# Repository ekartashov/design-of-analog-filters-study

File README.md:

# Design of Analog Filters

**The analog front-end of a surface-EMG (muscle) sensor — designed, simulated, built and measured.**
Maturità thesis (independent research paper of the Swiss Gymnasium), *Liceo cantonale di Lugano 1*, school year **2021/2022**.

## 📄 Read the paper

| Edition | PDF | |
|---|---|---|
| 🇬🇧 **English** | [`…_EN_optimized.pdf`](LAM/LAM_Design_dei_filtri_analogici/LAM_Design_dei_filtri_analogici_EN_optimized.pdf) | **recommended entry point** |
| 🇮🇹 **Italiano** | [`…_2022-optimized.pdf`](LAM/LAM_Design_dei_filtri_analogici/LAM_Design_dei_filtri_analogici_2022-optimized.pdf) | **the original** |
| 🇷🇺 **Русский** | [`…_RU_optimized.pdf`](LAM/LAM_Design_dei_filtri_analogici/LAM_Design_dei_filtri_analogici_RU_optimized.pdf) | translation |

> **On languages.** The paper was written and submitted in **Italian**; that is the original. The English and Russian editions are complete 2026 re-translations of the same text and figures (AI-assisted, human-revised; interpretation spots are flagged in the sources as `% TRANSLATOR NOTE:` comments). Cite the Italian original.

> **On the context.** This was completed as a **maturità paper for the Gymnasium** (high-school leaving qualification) during the 2021/2022 school year at the Cantonal Lyceum of Lugano (Liceo cantonale di Lugano 1, Switzerland). It was an entirely self-directed project: **no university studies and no related formal courses had informed it** — the filter theory, the circuit design and the measurement methodology were studied independently for this work.

## What this project is

A from-scratch development of the analog signal chain of an electromyographic sensor — the weak muscle signal picked up by skin electrodes, conditioned and digitized:

- **Theory built up from first principles** in the paper: systems, transfer functions, poles/zeros, Bode plots, passive and active filter stages (Butterworth, Chebyshev, Bessel), op-amp circuits, noise/EMI, discretization, ADC resolution
- **Full hardware**: 3 custom PCBs (sensor board, electrode board, power-source board) designed in KiCad, built as photographed prototypes
- **Real measurements**: 8-channel recordings of hand-muscle contractions, with amplitude/height adjustability demonstrated and FFT gesture analysis — including a 66 MB raw acquisition dataset
- **81 pages, 121 natively-drawn plots** (pgfplots — Bode/transient/pole-zero figures compiled from the same CSVs as the measurements), 74 sources

## Repository layout

```
LAM/LAM_Design_dei_filtri_analogici/    the paper: .tex sources, .bib, media/, datasets/, and the 3 optimized PDFs
LAM/secondary/                          working material: filter-design notes, sensor-board diagram, FFT notebooks
kicad/emg_sensor_board/                 hardware project: 3 PCBs + schematics, 3D renders, sim notes, BOM
scripts/devbox/  distrobox.ini          reproducible TeX toolchain (podman + distrobox, image pinned by digest)
notes/                                  provenance and translation-workflow notes
```

## Building the paper

The toolchain is containerized (LuaLaTeX + biber + TeX Live 2025 in a Debian devbox):

```bash
./scripts/devbox/setup-devbox.bash            # build image + create the box (once; requires podman)
distrobox enter devbox_lam_latex -- bash -c '
  cd LAM/LAM_Design_dei_filtri_analogici && latexmk -lualatex -shell-escape'
```

Figures are TikZ-externalized into `cache/` (gitignored) — a cold build renders all ~120 of them once, incremental rebuilds then take minutes. The PDFs committed here are Ghostscript-optimized (~19 MB each, visually lossless); unoptimized builds are ~150 MB and are left out of the repo.

**Cleaning up afterwards.** `scripts/clean.sh` removes the junk a build leaves behind (LaTeX intermediates, `latexmk` strays, the ~150 MB unoptimized PDFs) while keeping the three `_optimized.pdf` deliverables, the 2022 original and all sources; `scripts/clean.sh --deep` additionally drops the `cache/` figures.

**Rebuilding the smaller documents.** The standalone working notes under `LAM/secondary/` (each folder is a tiny LaTeX document: the 8-channel plot sheet `plots/Standalone.tex`, `Q_Factor/`, `Analogue_filter_design/`, `Circuit/SensorBoard_circuit_diagram.tex`) and the KiCad print plot are *build outputs* and are not committed — regenerate them with `latexmk -lualatex -shell-escape <name>.tex` in the devbox, or re-export the plot from the KiCad project. The PDFs that **are** committed under `media/` (Maple exports, Ideasheets, PCB crops, TI app-notes) are *inputs*: the Maple worksheets did not survive, so those ten Maple PDFs are irreplaceable. The `guide/Order_*.pdf` is a JLC order record, kept as a document.

## Measurement datasets

In `LAM/LAM_Design_dei_filtri_analogici/datasets/`:

| Folder | Contents |
|---|---|
| `cf_fft_hand_muscles/` | 8-channel hand-contraction acquisitions (incl. per-session raw dumps and a 66 MB `data.txt`), FFT analysis notebook |
| `result/` | the three plotted measured signals (`gr1`–`gr3.csv` — the teal traces in Fig. 54) |
| `s_plot_example_data/`, `s_plot_log_example_data/` | filter-response datasets behind the Bode/transient plots |
| `ecg_example_data/` | ECG example recorded through the EMG sensor |

## License

© 2021–2026 Evgeny Kartashov — [CC BY 4.0](LICENSE.md). Third-party images (e.g. Arduino/ESP32 board photos, datasheet figures) keep their sources' licenses as credited in the paper's source lists.

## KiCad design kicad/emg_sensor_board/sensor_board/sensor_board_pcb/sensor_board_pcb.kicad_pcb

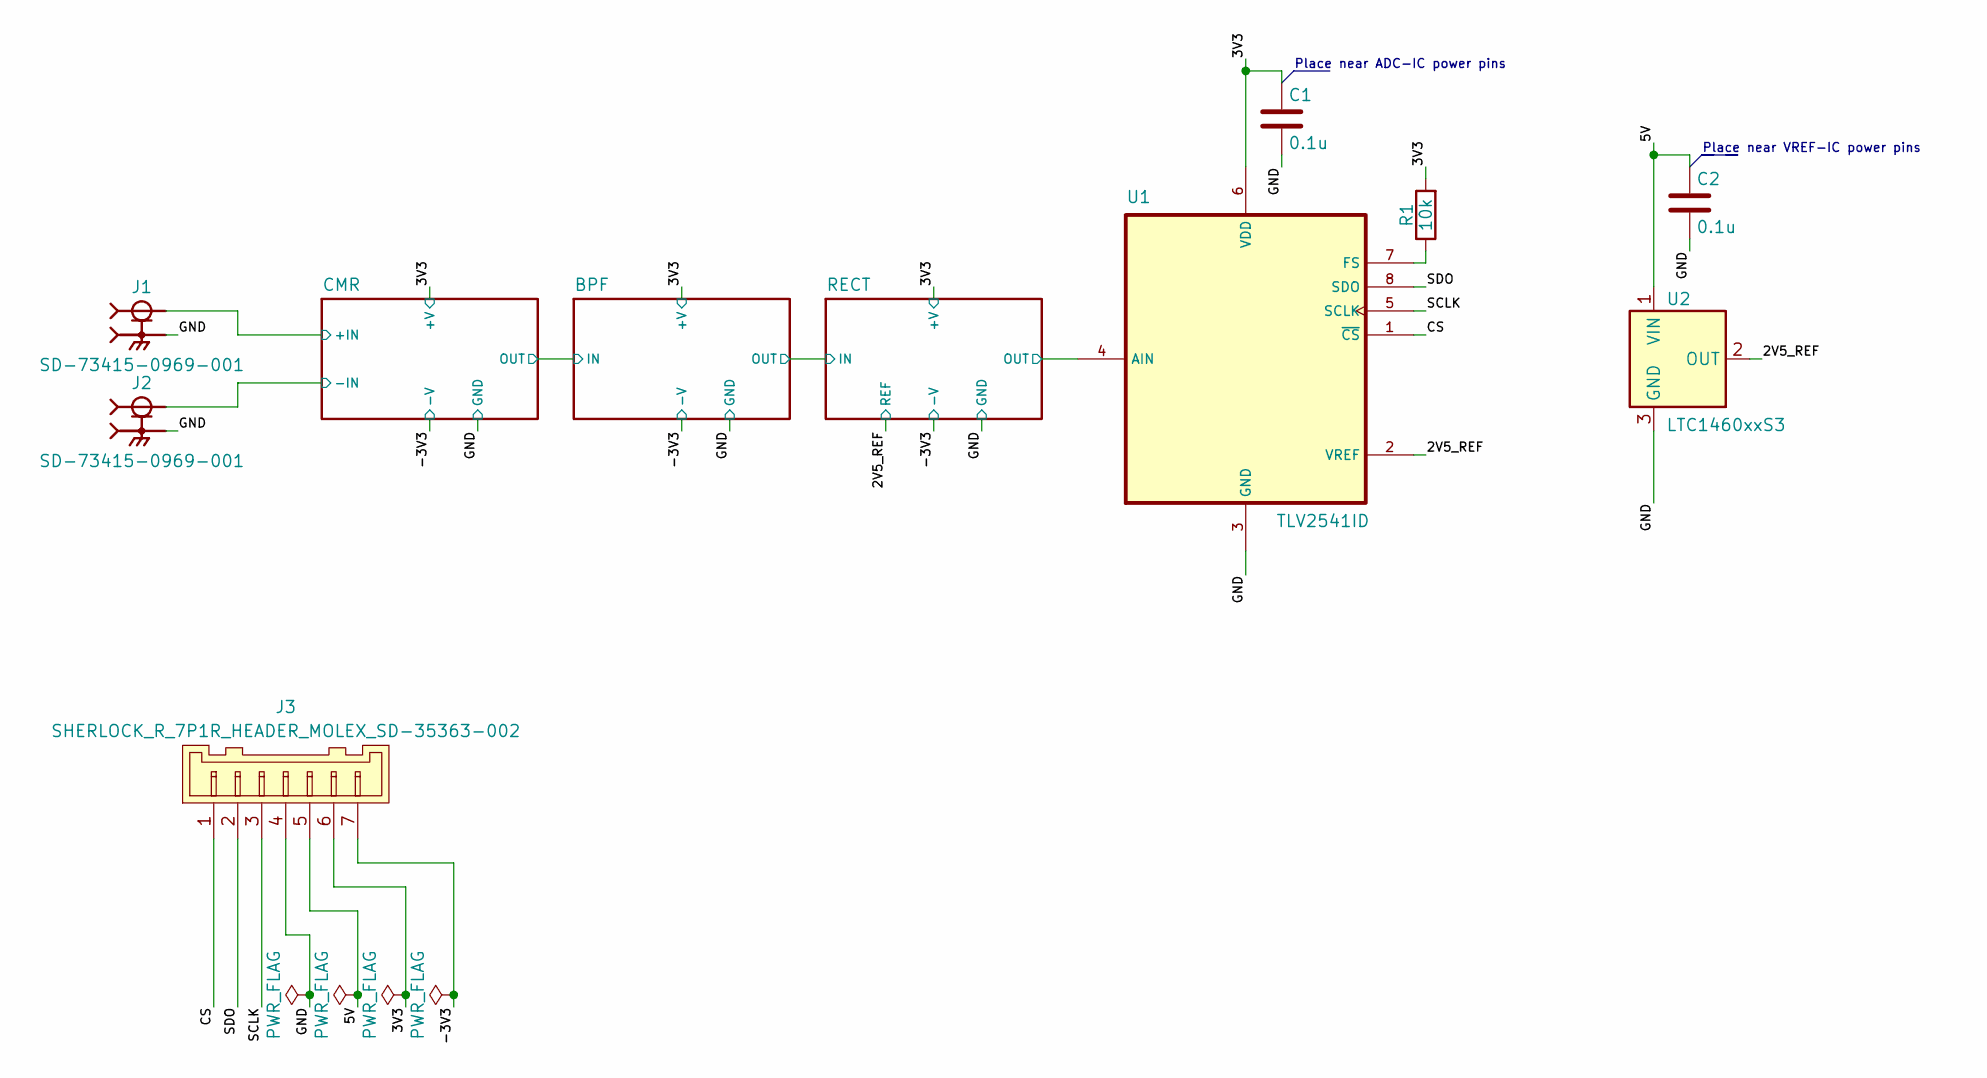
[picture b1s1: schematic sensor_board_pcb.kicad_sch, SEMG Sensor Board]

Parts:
C1, C2: 0.1u; C_0603_1608Metric_Pad1.08x0.95mm_HandSolder
J1, J2: SD-73415-0969-001; MMCX_MOLEX_SD-73415-0969-001
J3: SHERLOCK_R_7P1R_HEADER_MOLEX_SD-35363-002
R1: 10k; R_0603_1608Metric_Pad0.98x0.95mm_HandSolder
U1: TLV2541ID; SOIC-8_3.9x4.9mm_P1.27mm
U2: LTC1460xxS3; SOT-23

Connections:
/2V5_REF: U1.2 (VREF), U2.2 (OUT); also elsewhere on the board
/3V3: C1.1, J3.6, R1.2, U1.6 (VDD); also elsewhere on the board
/5V: C2.1, J3.5, U2.1 (VIN)
/-3V3: J3.7; also elsewhere on the board
/CMR/+IN: J1.1 (IN); also elsewhere on the board
/CMR/-IN: J2.1 (IN); also elsewhere on the board
/CS: J3.1, U1.1 (~CS)
/GND: C1.2, C2.2, J1.S1 (EXT1), J1.S2 (EXT2), J2.S1 (EXT1), J2.S2 (EXT2), J3.4, U1.3 (GND), U2.3 (GND); also elsewhere on the board
/RECT/OUT: U1.4 (AIN); also elsewhere on the board
/SCLK: J3.3, U1.5 (SCLK)
/SDO: J3.2, U1.8 (SDO)
unnamed: R1.1, U1.7 (FS)

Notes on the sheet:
Place near ADC-IC power pins
Place near VREF-IC power pins

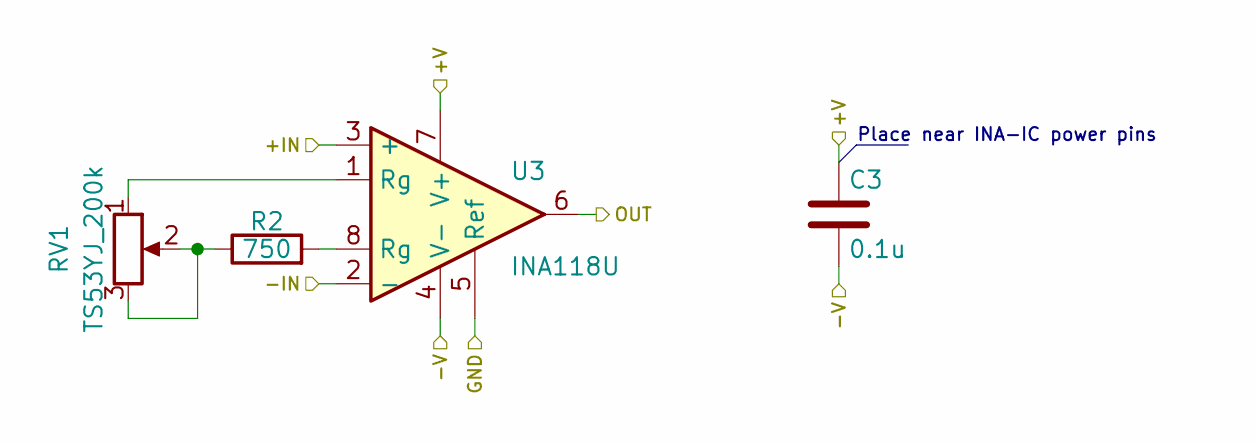
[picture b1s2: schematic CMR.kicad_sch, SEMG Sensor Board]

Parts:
C3: 0.1u; C_0603_1608Metric_Pad1.08x0.95mm_HandSolder
R2: 750; R_0603_1608Metric_Pad0.98x0.95mm_HandSolder
RV1: TS53YJ_200k; Potentiometer_Vishay_TS53YJ_Vertical
U3: INA118U; SOIC-8_3.9x4.9mm_P1.27mm

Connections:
/3V3: C3.1, U3.7 (V+); also elsewhere on the board
/-3V3: C3.2, U3.4 (V-); also elsewhere on the board
/BPF/IN: U3.6; also elsewhere on the board
/CMR/+IN: U3.3 (+); also elsewhere on the board
/CMR/-IN: U3.2 (-); also elsewhere on the board
/GND: U3.5 (Ref); also elsewhere on the board
unnamed: R2.1, RV1.2, RV1.3
unnamed: R2.2, U3.8 (Rg)
unnamed: RV1.1, U3.1 (Rg)

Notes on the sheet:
Place near INA-IC power pins

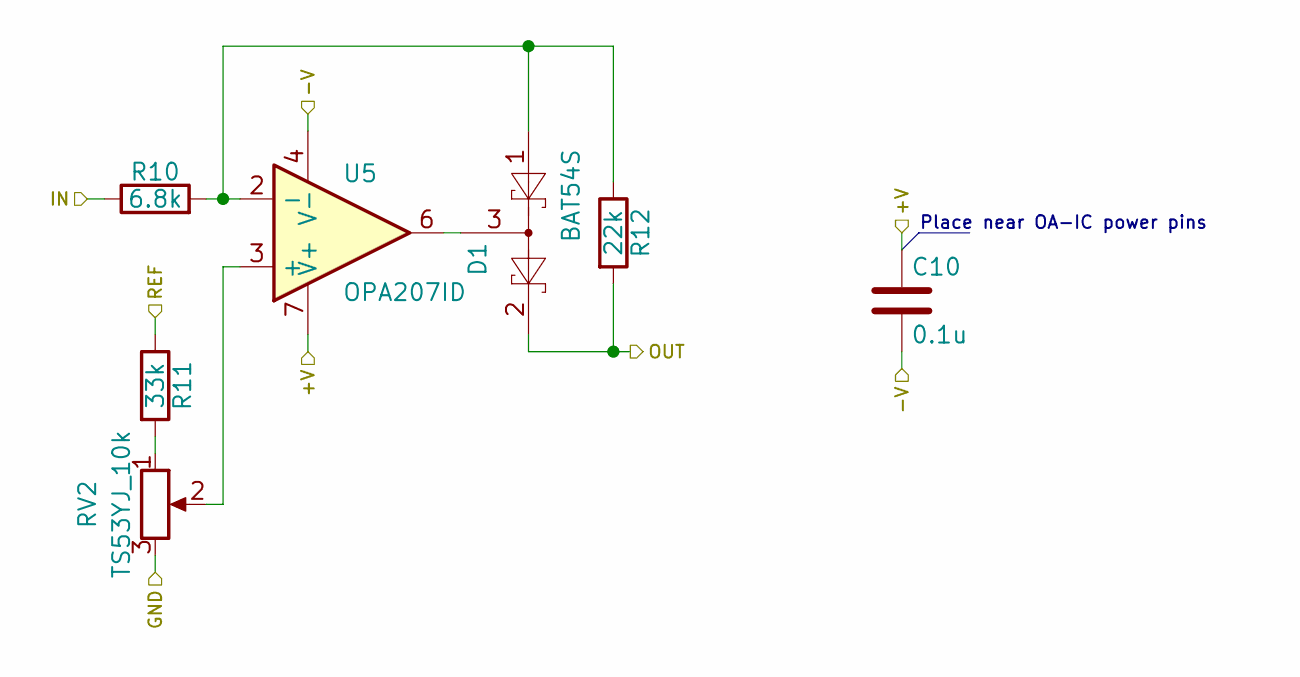
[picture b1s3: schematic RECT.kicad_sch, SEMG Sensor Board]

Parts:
C10: 0.1u; C_0603_1608Metric_Pad1.08x0.95mm_HandSolder
D1: BAT54S; SOT-23
R10: 6.8k; R_0603_1608Metric_Pad0.98x0.95mm_HandSolder
R11: 33k; R_0603_1608Metric_Pad0.98x0.95mm_HandSolder
R12: 22k; R_0603_1608Metric_Pad0.98x0.95mm_HandSolder
RV2: TS53YJ_10k; Potentiometer_Vishay_TS53YJ_Vertical
U5: OPA207ID; SOIC-8_3.9x4.9mm_P1.27mm

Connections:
/2V5_REF: R11.1; also elsewhere on the board
/3V3: C10.1, U5.7 (V+); also elsewhere on the board
/-3V3: C10.2, U5.4 (V-); also elsewhere on the board
/BPF/OUT: R10.1; also elsewhere on the board
/GND: RV2.3; also elsewhere on the board
/RECT/OUT: D1.2, R12.2; also elsewhere on the board
unnamed: D1.1, R10.2, R12.1, U5.2 (-)
unnamed: D1.3, U5.6
unnamed: R11.2, RV2.1
unnamed: RV2.2, U5.3 (+)

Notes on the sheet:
Place near OA-IC power pins

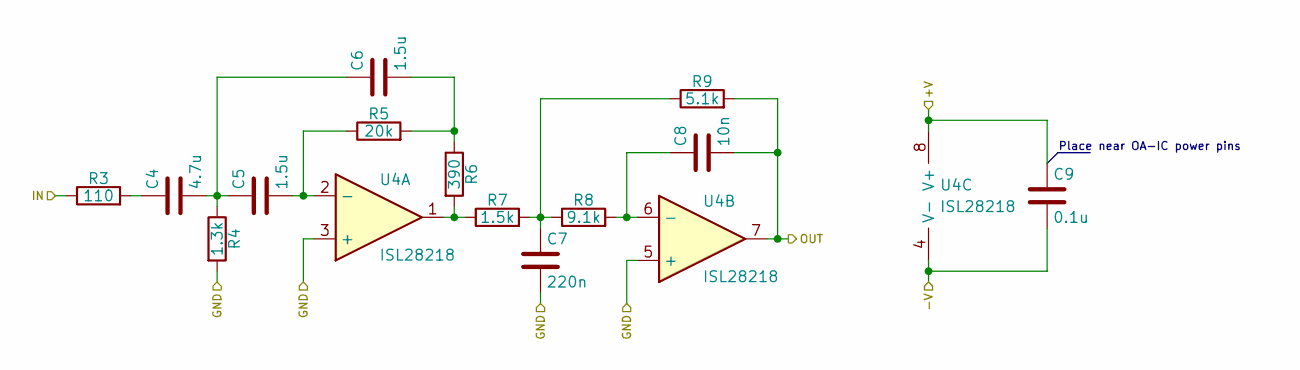
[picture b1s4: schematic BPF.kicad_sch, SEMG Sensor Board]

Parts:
C4: 4.7u; C_0603_1608Metric_Pad1.08x0.95mm_HandSolder
C5, C6: 1.5u; C_0603_1608Metric_Pad1.08x0.95mm_HandSolder
C7: 220n; C_0603_1608Metric_Pad1.08x0.95mm_HandSolder
C8: 10n; C_0603_1608Metric_Pad1.08x0.95mm_HandSolder
C9: 0.1u; C_0603_1608Metric_Pad1.08x0.95mm_HandSolder
R3: 110; R_0603_1608Metric_Pad0.98x0.95mm_HandSolder
R4: 1.3k; R_0603_1608Metric_Pad0.98x0.95mm_HandSolder
R5: 20k; R_0603_1608Metric_Pad0.98x0.95mm_HandSolder
R6: 390; R_0603_1608Metric_Pad0.98x0.95mm_HandSolder
R7: 1.5k; R_0603_1608Metric_Pad0.98x0.95mm_HandSolder
R8: 9.1k; R_0603_1608Metric_Pad0.98x0.95mm_HandSolder
R9: 5.1k; R_0603_1608Metric_Pad0.98x0.95mm_HandSolder
U4: ISL28218; SOIC-8_3.9x4.9mm_P1.27mm

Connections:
/3V3: C9.1, U4.8 (V+); also elsewhere on the board
/-3V3: C9.2, U4.4 (V-); also elsewhere on the board
/BPF/IN: R3.1; also elsewhere on the board
/BPF/OUT: C8.2, R9.2, U4.7; also elsewhere on the board
/GND: C7.2, R4.2, U4.3 (+), U4.5 (+); also elsewhere on the board
unnamed: C4.1, R3.2
unnamed: C4.2, C5.1, C6.1, R4.1
unnamed: C5.2, R5.1, U4.2 (-)
unnamed: C6.2, R5.2, R6.1
unnamed: C7.1, R7.2, R8.1, R9.1
unnamed: C8.1, R8.2, U4.6 (-)
unnamed: R6.2, R7.1, U4.1

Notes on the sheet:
Place near OA-IC power pins

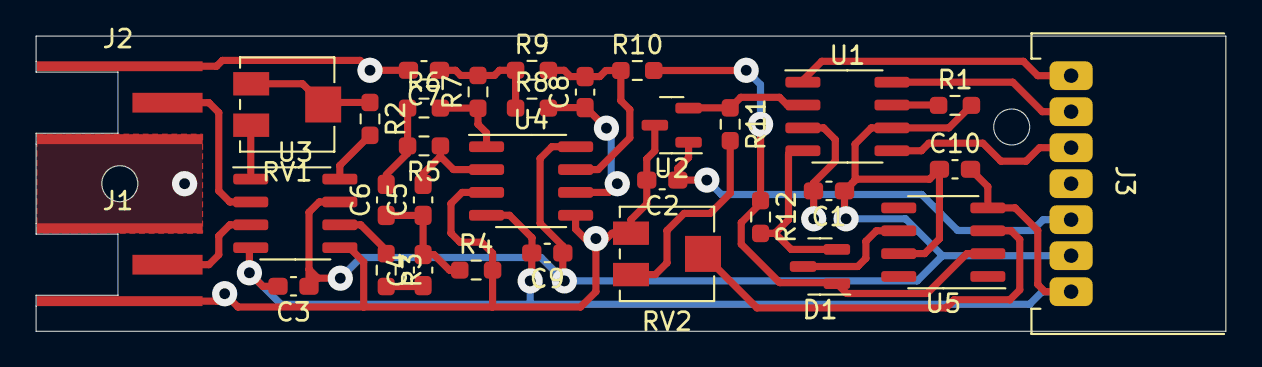
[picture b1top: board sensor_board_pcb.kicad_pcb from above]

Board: 2 copper layers, 66.1 x 16.4 mm, 33 parts (0 on the bottom side), 28 nets.
